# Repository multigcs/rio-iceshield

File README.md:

# rio-iceshield
6 Axis LinuxCNC-RIO Raspberry-PI FPGA-Hat - kicad project

**experimental**

## software / gateware
https://github.com/multigcs/riocore

## BOM

## Forum
German: https://www.cnc-aus-holz.at/index.php?thread/3130-experimente-mit-linux-cnc-auf-raspi-und-ice40-fpga-als-mesa-alternative/&postID=40335#post40335
English: https://forum.linuxcnc.org/18-computer/49142-linuxcnc-rio-realtimeio-for-linuxcnc-based-on-fpga-ice40-ecp5

## to provide a clock signal for the FPGA
```
gpio mode 7 clock
gpio clock 7 5000000
```

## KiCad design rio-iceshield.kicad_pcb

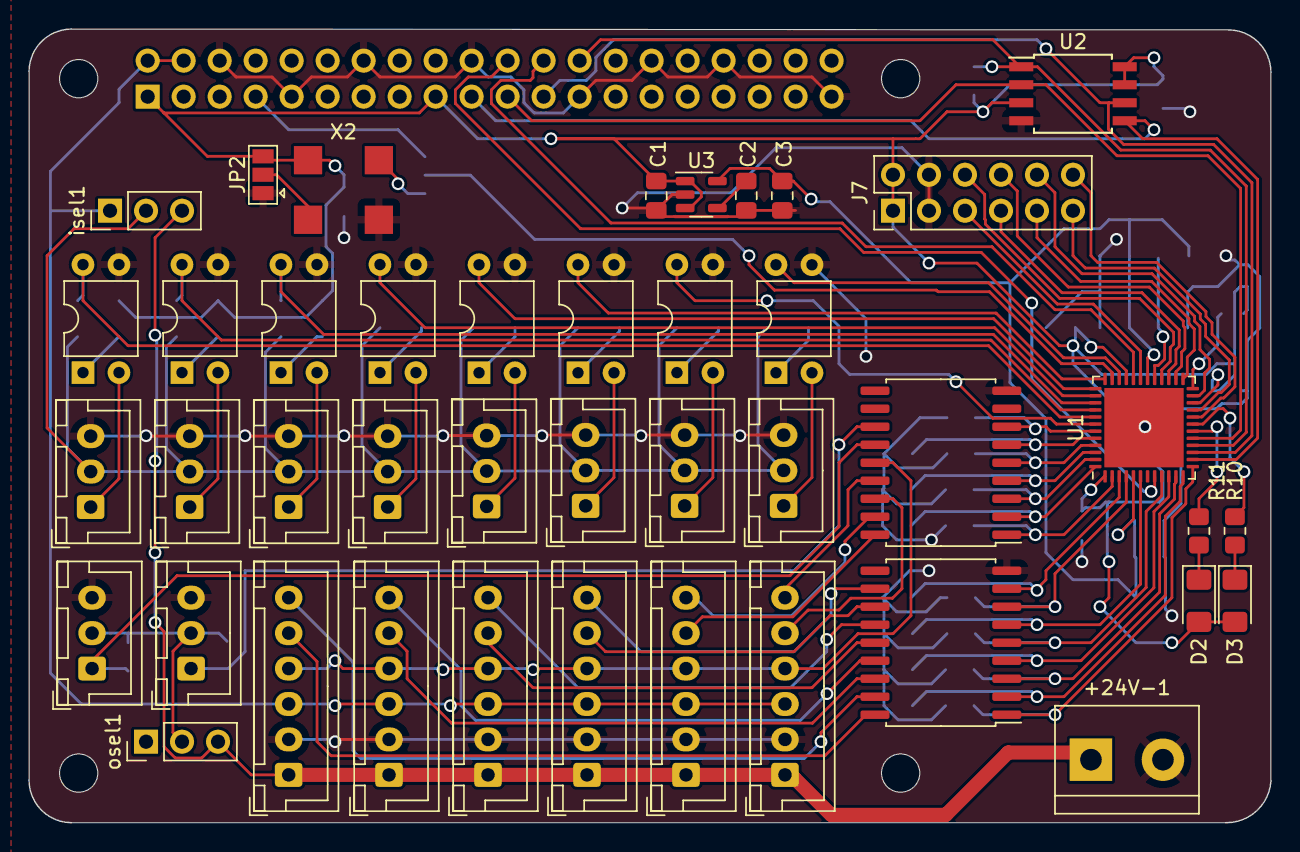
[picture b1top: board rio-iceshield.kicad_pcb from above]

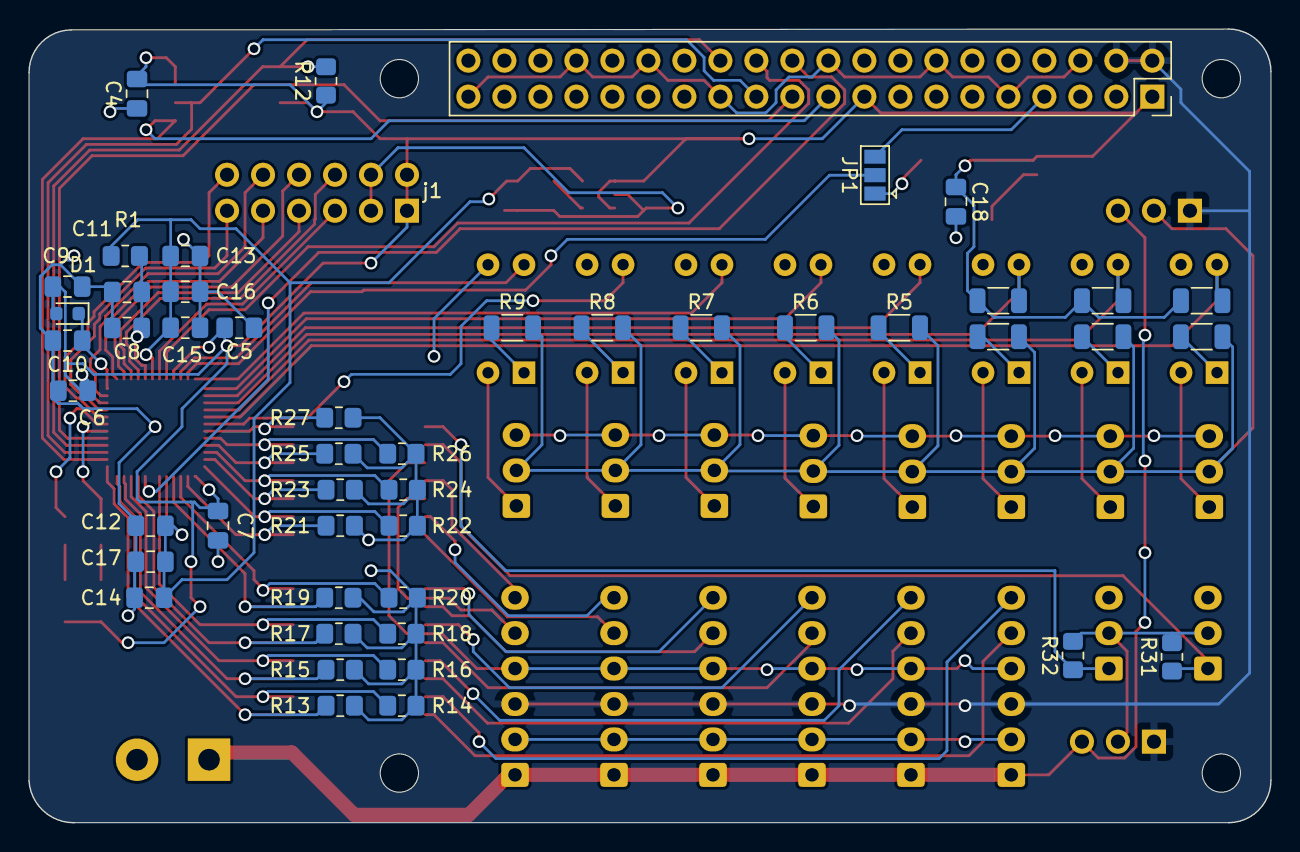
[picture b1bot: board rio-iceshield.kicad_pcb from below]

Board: 2 copper layers, 87.6 x 56.0 mm, 94 parts (48 on the bottom side), 86 nets.

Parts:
+24V-1: Screw_Terminal_01x02; TerminalBlock_bornier-2_P5.08mm
C1, C3: 4u7; C_0805_2012Metric_Pad1.18x1.45mm_HandSolder
C2, C13, C17: 10n; C_0805_2012Metric_Pad1.18x1.45mm_HandSolder
C4, C5, C6, C7, C8, C9, C10, C14, C16, C18: 100n; C_0805_2012Metric_Pad1.18x1.45mm_HandSolder
C11: 10u; C_0805_2012Metric_Pad1.18x1.45mm_HandSolder
C12, C15: 1u; C_0805_2012Metric_Pad1.18x1.45mm_HandSolder
D1: 1N 4148WT7 DII; D_0603_1608Metric
D2, D3: LED; LED_1206_3216Metric_Pad1.42x1.75mm_HandSolder
J2, J3, J4, J5, J6: Conn_01x06; JST_XH_B6B-XH-A_1x06_P2.50mm_Vertical
J7: Conn_02x06_Odd_Even; PinHeader_2x06_P2.54mm_Vertical
JP1, JP2: SolderJumper_3_Open; SolderJumper-3_P1.3mm_Open_Pad1.0x1.5mm
Jo1: Conn_01x06; JST_XH_B6B-XH-A_1x06_P2.50mm_Vertical
MH1, MH2, MH3, MH4: MountingHole_2.7mm_M2.5
R1: 100; R_0805_2012Metric_Pad1.20x1.40mm_HandSolder
R2, R3, R4, R5, R6, R7, R8, R9: 3K3; R_1206_3216Metric
R10, R11: 900; R_0805_2012Metric_Pad1.20x1.40mm_HandSolder
R12: 10k; R_0805_2012Metric_Pad1.20x1.40mm_HandSolder
R13, R14, R15, R16, R17, R18, R19, R20, R21, R22, R23, R24, R25, R26, R27: 20k; R_0805_2012Metric_Pad1.20x1.40mm_HandSolder
R28, R29, R30: 20K; R_1206_3216Metric
R31, R32: 3k3; R_0805_2012Metric_Pad1.20x1.40mm_HandSolder
U1: ICE40UP5K-SG48ITR; QFN-48-1EP_7x7mm_P0.5mm_EP5.6x5.6mm
U2: AT25SF041B-SHD 4 Mb; SOIC-8W_5.3x5.3mm_P1.27mm
U3: LD3985M122R_SOT23; SOT-23-5
U4, U5: ULN2803A; SOIC-18W_7.5x11.6mm_P1.27mm
U7, U8, U9, U10, U11, U12, U13, U14: PC817; DIP-4_W7.62mm
X2: XO91; Oscillator_SMD_EuroQuartz_XO91-4Pin_7.0x5.0mm
input1, input2, input3, input4, input5, input6, input7, input8: Conn_01x03; JST_XH_B3B-XH-A_1x03_P2.50mm_Vertical
isel1: Conn_01x03; PinHeader_1x03_P2.54mm_Vertical
j1: GPIO; PinSocket_2x20_P2.54mm_Vertical
osel1: Conn_01x03; PinHeader_1x03_P2.54mm_Vertical
output1, output2: Conn_01x03; JST_XH_B3B-XH-A_1x03_P2.50mm_Vertical

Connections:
1v2: C3.1, C12.1, C13.1, C14.1, C15.1, C16.1, C17.1, R1.1, U1.5 (VCC), U1.30 (VCC), U3.5 (VOUT)
2: R21.2, U1.2 (IOB_6a), U5.1 (I1)
2v5: C10.1, D1.1 (K), U1.24 (VPP_2V5)
3: R20.2, U1.3 (IOB_9b), U4.8 (I8)
3v3: C1.1, C4.2, C5.2, C6.2, C7.2, C9.1, C18.1, D1.2 (A), D2.2 (A), D3.2 (A), J7.1, J7.2, JP2.3 (B), R12.1, R28.1, R29.1, R30.1, U1.1 (VCCIO_2), U1.22 (SPI_VCCIO1), U1.33 (VCCIO_0), U2.3 (~WP/IO2), U2.7 (~HOLD/IO3), U2.8 (VCC), U3.1 (VIN), U3.3 (INH), X2.4 (V+), j1.1, j1.17
4: R19.2, U1.4 (IOB_8a), U4.7 (I7)
5v: J2.3, J3.3, J4.3, J5.3, J6.3, Jo1.3, isel1.1, j1.2, j1.4, osel1.1
6: R18.2, U1.6 (IOB_13b), U4.6 (I6)
9: R17.2, U1.9 (IOB_16a), U4.5 (I5)
10: R16.2, U1.10 (IOB_18a), U4.4 (I4)
11: R15.2, U1.11 (IOB_20a), U4.3 (I3)
12: R14.2, U1.12 (IOB_22a), U4.2 (I2)
12v: +24V-1.1, J2.1, J3.1, J4.1, J5.1, J6.1, Jo1.1, isel1.3, osel1.3
13: R13.2, U1.13 (IOB_24a), U4.1 (I1)
18: R11.1, U1.18 (IOB_31b)
19: R10.1, U1.19 (IOB_29b)
20: J7.12, U1.20 (IOB_25b_G3)
21: J7.11, U1.21 (IOB_23b)
23: J7.10, U1.23 (IOT_37a)
25: J7.9, U1.25 (IOT_36b)
26: J7.8, U1.26 (IOT_39a)
27: J7.7, U1.27 (IOT_38b)
28: J7.6, U1.28 (IOT_41a)
31: J7.5, U1.31 (IOT_42b)
32: U1.32 (IOT_43a), j1.24
34: U1.34 (IOT_44b), U14.4
35: JP1.2 (C), U1.35 (IOT_46b_G0)
36: U1.36 (IOT_48b), U12.4
37: U1.37 (IOT_45a_G1), U11.4
38: U1.38 (IOT_50b), U10.4
39: R28.2, U1.39 (RGB0), U9.4
40: R29.2, U1.40 (RGB1), U8.4
41: R30.2, U1.41 (RGB2), U7.4
42: U1.42 (IOT_51a), U13.4
43: R27.2, U1.43 (IOT_49a), U5.7 (I7)
44: R26.2, U1.44 (IOB_3b_G6), U5.6 (I6)
45: R25.2, U1.45 (IOB_5b), U5.5 (I5)
46: R24.2, U1.46 (IOB_0a), U5.4 (I4)
47: R23.2, U1.47 (IOB_2a), U5.3 (I3)
48: R22.2, U1.48 (IOB_4a), U5.2 (I2)
CRESET: U1.8 (~CRESET), j1.22
unnamed: D2.1 (K), R11.2
unnamed: D3.1 (K), R10.2
unnamed: JP1.1 (A), X2.3 (OUT)
unnamed: JP2.2 (C), X2.1 (EN)
unnamed: R2.1, U7.1
unnamed: R3.1, U8.1
unnamed: R4.1, U9.1
unnamed: R5.1, U10.1
unnamed: R6.1, U11.1
unnamed: R7.1, U12.1
unnamed: R8.1, U13.1
unnamed: R9.1, U14.1
unnamed: C8.1, C11.1, R1.2, U1.29 (VCCPLL)
unnamed: C2.1, U3.4 (BYP)
unnamed: U7.2, input1.1
unnamed: U8.2, input2.1
unnamed: U9.2, input3.1
unnamed: U10.2, input4.1
unnamed: U11.2, input5.1
unnamed: U12.2, input6.1
unnamed: U13.2, input7.1
unnamed: U14.2, input8.1
RPI_CLK: JP1.3 (B), j1.7
SPI_CS1: R12.2, U1.16 (IOB_35b_SPI_SS), U2.1 (~CS), j1.26
SPI_MISO: U1.17 (IOB_33b_SPI_SI), U2.2 (SO/IO1), j1.21
SPI_MOSI: U1.14 (IOB_32a_SPI_SO), U2.5 (SI/IO0), j1.19
SPI_SCK: U1.15 (IOB_34a_SPI_SCK), U2.6 (SCK), j1.23
enable: J2.4, J3.4, J4.4, J5.4, J6.4, Jo1.4, U5.14 (O5)
gnd: +24V-1.2, C1.2, C2.2, C3.2, C4.1, C5.1, C6.1, C7.1, C8.2, C9.2, C10.2, C11.2, C12.2, C13.2, C14.2, C15.2, C16.2, C17.2, C18.2, J2.2, J3.2, J4.2, J5.2, J6.2, J7.3, J7.4, JP2.1 (A), Jo1.2, R13.1, R14.1, R15.1, R16.1, R17.1, R18.1, R19.1, R20.1, R21.1, R22.1, R23.1, R24.1, R25.1, R26.1, R27.1, U1.49 (GND), U2.4 (GND), U3.2 (GND), U4.9 (GND), U5.9 (GND), U7.3, U8.3, U9.3, U10.3, U11.3, U12.3, U13.3, U14.3, X2.2 (GND), input1.3, input2.3, input3.3, input4.3, input5.3, input6.3, input7.3, input8.3, j1.6, j1.9, j1.14, j1.20, j1.25, j1.30, j1.34, j1.39, output1.3, output2.3
in_power: R2.2, R3.2, R4.2, R5.2, R6.2, R7.2, R8.2, R9.2, input1.2, input2.2, input3.2, input4.2, input5.2, input6.2, input7.2, input8.2, isel1.2
j1_dir: Jo1.6, U4.17 (O2)
j1_step: Jo1.5, U4.18 (O1)
j2_dir: J2.6, U4.15 (O4)
j2_step: J2.5, U4.16 (O3)
j3_dir: J3.6, U4.13 (O6)
j3_step: J3.5, U4.14 (O5)
j4_dir: J4.6, U4.11 (O8)
j4_step: J4.5, U4.12 (O7)
j5_dir: J5.6, U5.17 (O2)
j5_step: J5.5, U5.18 (O1)
j6_dir: J6.6, U5.15 (O4)
j6_step: J6.5, U5.16 (O3)
out1: R31.1, U5.13 (O6), output1.1
out2: R32.1, U5.12 (O7), output2.1
out_power: R31.2, R32.2, osel1.2, output1.2, output2.2

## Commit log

2024-07-03 initial release
2024-07-03 adding image
2024-07-07 adding missing in/out powerlines
2024-07-16 pdate readme
2024-08-06 replacing spi-flash package
2024-08-06 updaing readme
2024-08-06 adding pulldowns to outputs / fixing uln gnd's
2024-08-06 other diode (i used in on my test-board)
2024-08-06 adding pullups to in1-3
2024-08-06 adding pullups to out1-2
